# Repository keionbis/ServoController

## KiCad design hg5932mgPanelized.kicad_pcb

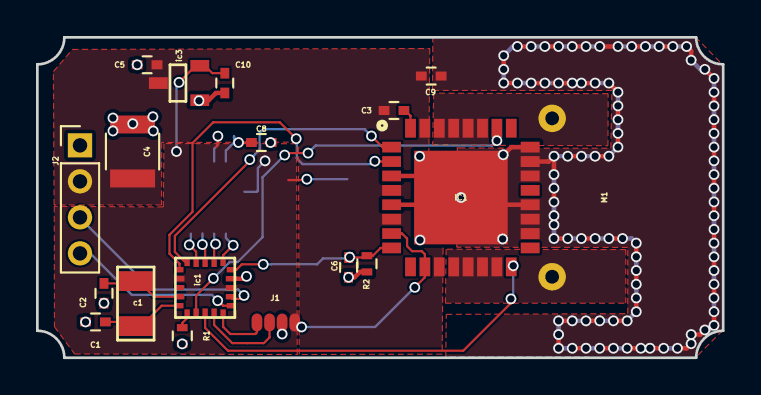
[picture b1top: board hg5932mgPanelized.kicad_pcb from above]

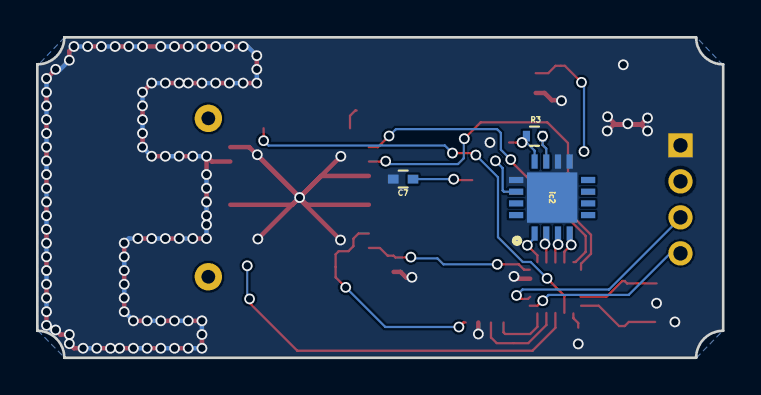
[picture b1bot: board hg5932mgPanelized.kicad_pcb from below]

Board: 2 copper layers, 38.1 x 17.8 mm, 21 parts (3 on the bottom side), 23 nets.

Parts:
C1, C2, C3, C5, C6, C7, C8, C9, C10: C; C_0402
C4: C; C_1210
IC1: MC33926; QFN80P800X800X220-33N
J1: Conn_01x04; 1x4Pads
J2: Conn_01x04; Pin_Header_Straight_1x04_Pitch2.00mm
M1: hv5932mgMotor
R1, R2, R3: R; R_0402
c1: ECX-31B
ic1: stm32l011; stm8l15
ic2: AS5055a; QFN65P400X400X90-17N
ic3: AP2120N

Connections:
+3V3: C7.1, C10.2, IC1.7, IC1.10, J1.1, R3.1, ic1.4, ic1.13, ic2.11, ic2.14, ic3.3
+BATT: C3.2, C4.1, C5.1, C9.2, IC1.4, IC1.6, IC1.11, IC1.31, J2.2, ic3.1
A: IC1.12, IC1.13, IC1.14, IC1.15, M1.1
B: IC1.27, IC1.28, IC1.29, IC1.30, M1.2
CS: ic1.7, ic2.4
D1: IC1.26, ic1.19
D2: IC1.16, ic1.18
FB: C6.2, IC1.8, R2.2, ic1.11
GND: C1.2, C2.2, C4.2, C5.2, C6.1, C7.2, C8.2, C9.1, C10.1, IC1.3, IC1.5, IC1.18, IC1.19, IC1.20, IC1.22, IC1.23, IC1.24, IC1.33, J1.2, J2.1, R1.2, R2.1, ic1.12, ic2.9, ic2.10, ic2.13, ic2.17, ic3.2
IN1: IC1.2, ic1.5
IN2: IC1.1, ic1.6
MISO: ic1.9, ic2.2
MOSI: ic1.10, ic2.1
unnamed: C3.1, IC1.32
unnamed: C8.1, R3.2, ic2.12
unnamed: R1.1, ic1.20
OSCIN: C1.1, c1.1, ic1.1
OSCOUT: C2.1, c1.2, ic1.2
SCK: ic1.8, ic2.3
SCL: J2.3, ic1.14
SDA: J2.4, ic1.15
SWCLK: J1.3, ic1.17
SWDIO: J1.4, ic1.16

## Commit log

2018-06-12 Rev 1
